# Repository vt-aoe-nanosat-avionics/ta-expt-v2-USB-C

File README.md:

# ta-expt-USB-C
This is a revised version of the Tartan Artibeus Experimental Board with USB C integration.

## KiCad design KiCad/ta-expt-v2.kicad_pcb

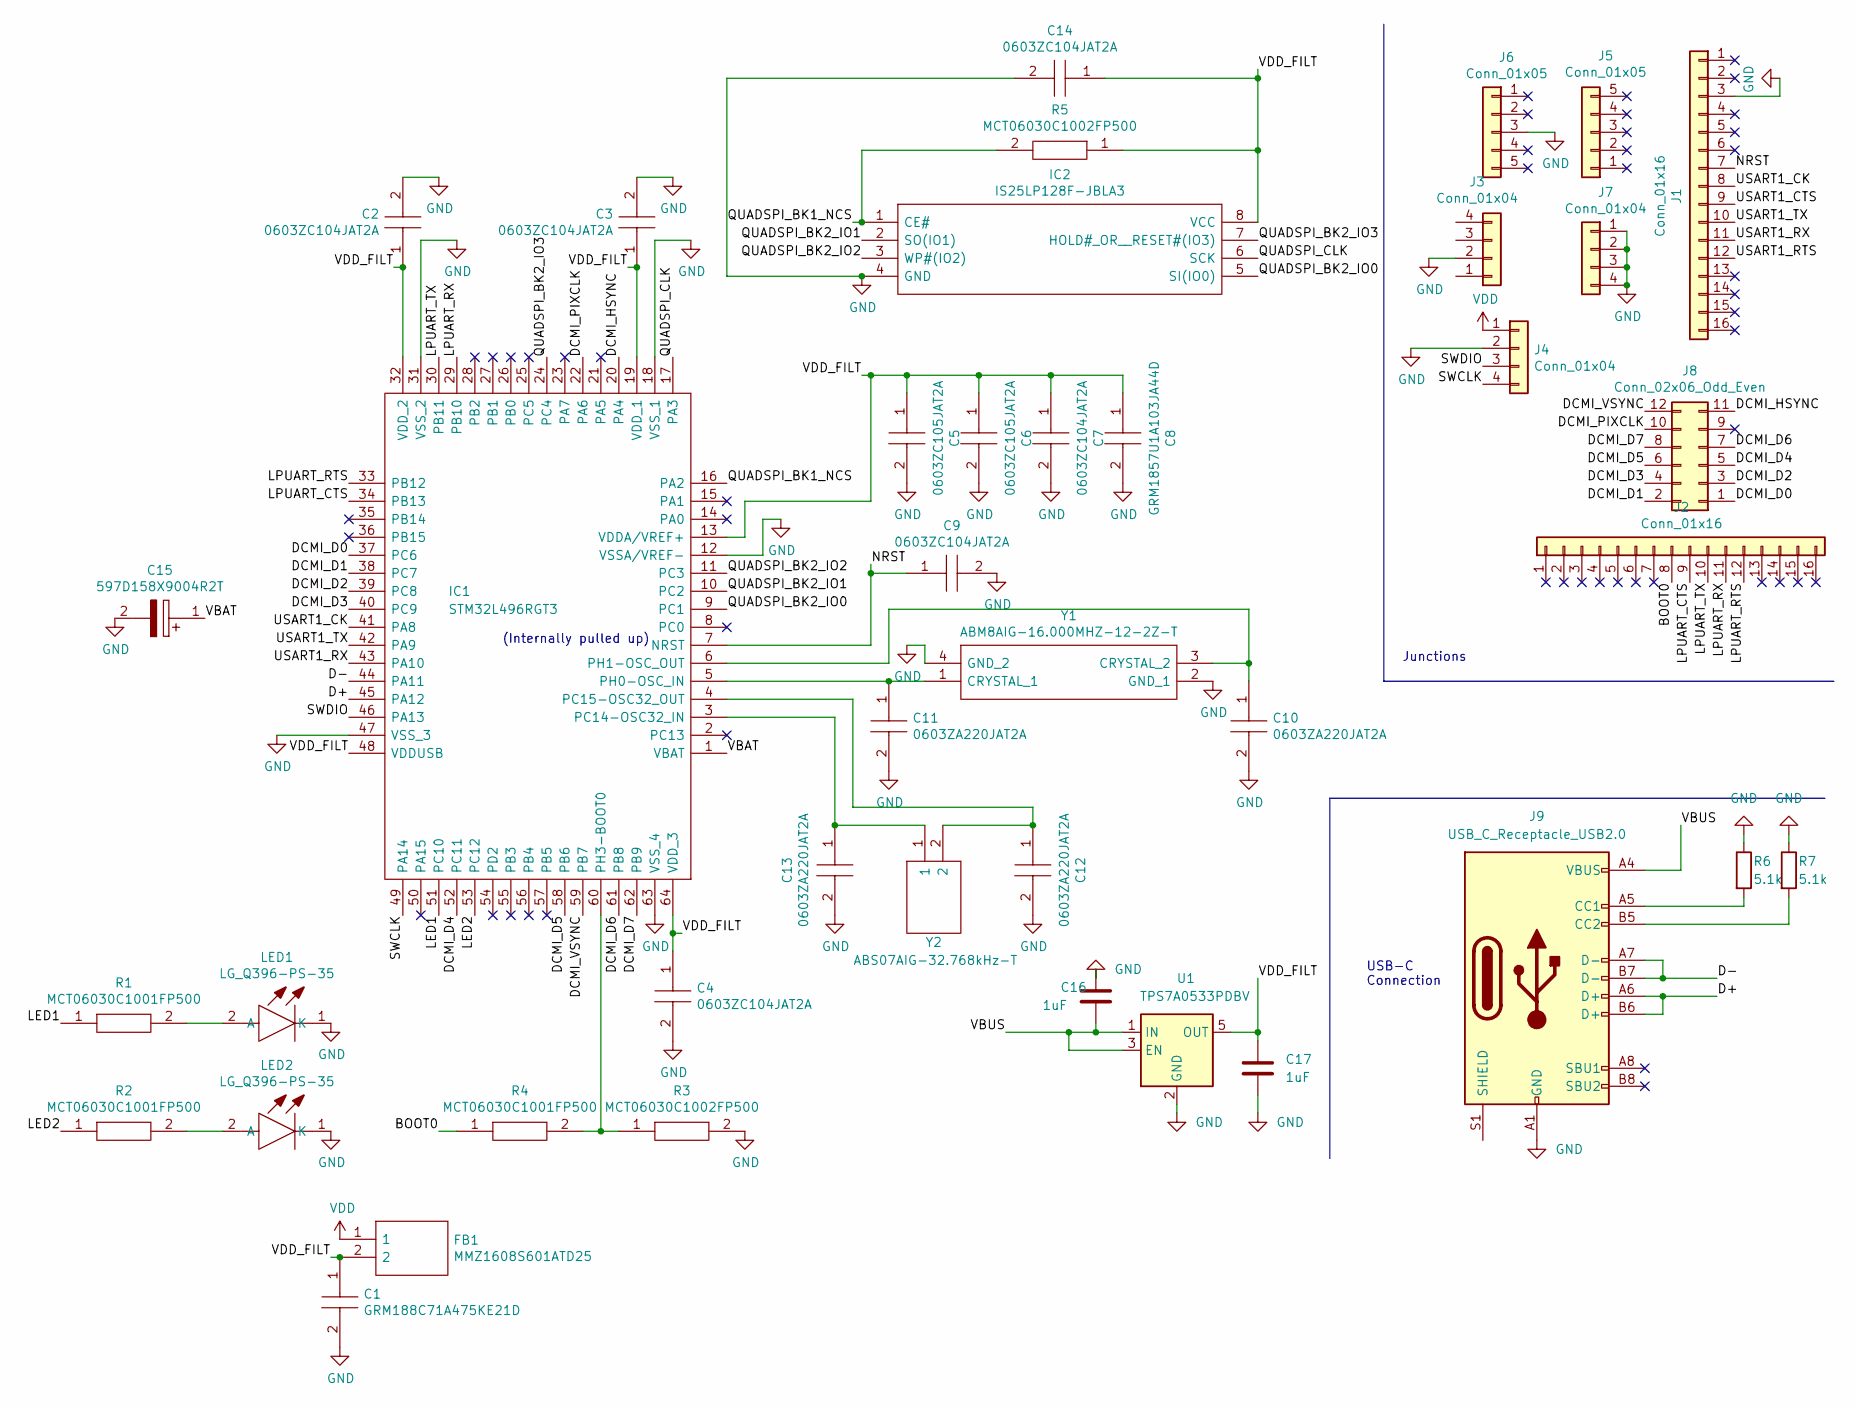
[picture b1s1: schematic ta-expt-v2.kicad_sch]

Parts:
C1: GRM188C71A475KE21D; CAPC1608X90N; Manufacturer_Part_Number GRM188C71A475KE21D; Mouser Part Number 81-GRM188C71A475KE2D
C2, C3, C4, C7, C9, C14: 0603ZC104JAT2A; CAPC1608X90N; Manufacturer_Part_Number 0603ZC104JAT2A; Mouser Part Number 581-0603ZC104JAT2A
C5, C6: 0603ZC105JAT2A; CAPC1608X90N; Manufacturer_Part_Number 0603ZC105JAT2A; Mouser Part Number 581-0603ZC105JAT2A
C8: GRM1857U1A103JA44D; CAPC1608X50N; Manufacturer_Part_Number GRM1857U1A103JA44D; Mouser Part Number 81-GRM1857U1A103JA4D
C10, C11, C12, C13: 0603ZA220JAT2A; CAPC1608X90N; Manufacturer_Part_Number 0603ZA220JAT2A; Mouser Part Number 581-0603ZA220JAT2A
C15: 597D158X9004R2T; CAPPC5660X400N; Manufacturer_Part_Number 597D158X9004R2T; Mouser Part Number 71-597D158X9004R2T
C16, C17: 1uF; CAPC1608X90N
FB1: MMZ1608S601ATD25; BEADC1608X95N; Manufacturer_Part_Number MMZ1608S601ATD25; Mouser Part Number 810-MMZ1608S601ATD25
IC1: STM32L496RGT3; QFP50P1200X1200X160-64N; Manufacturer_Part_Number STM32L496RGT3; Mouser Part Number 511-STM32L496RGT3
IC2: IS25LP128F-JBLA3; SOIC127P790X216-8N; Manufacturer_Part_Number IS25LP128F-JBLA3; Mouser Part Number 870-IS25LP128F-JBLA3
J1, J2: Conn_01x16; PinSocket_1x16_TartanArtibeus
J3, J4: Conn_01x04; PinSocket_4x1_TartanArtibeus
J5, J6: Conn_01x05; PinSocket_1x5_TartanArtibeus
J7: Conn_01x04; MountingHoles_TartanArtibeus
J8: Conn_02x06_Odd_Even; PinSocket_6x2_TartanArtibeus
J9: USB_C_Receptacle_USB2.0; USB_C_CUSB31-CFM2AX-01-X
LED1, LED2: LG_Q396-PS-35; LGQ396PS35; Manufacturer_Part_Number LG Q396-PS-35; Mouser Part Number 720-LGQ396A3964
R1, R2, R4: MCT06030C1001FP500; RESC1608X55N; Manufacturer_Part_Number MCT06030C1001FP500; Mouser Part Number 594-MCT06030C1001FP5
R3, R5: MCT06030C1002FP500; RESC1608X55N; Manufacturer_Part_Number MCT06030C1002FP500; Mouser Part Number 594-MCT06030C1002FP5
R6, R7: 5.1k; RESC1608X55N
U1: TPS7A0533PDBV; SOT-23-5
Y1: ABM8AIG-16.000MHZ-12-2Z-T; ABM8AIG25000MHZ122ZT3; Manufacturer_Part_Number ABM8AIG-16.000MHZ-12-2Z-T; Mouser Part Number 815-ABM8AIG16122ZT
Y2: ABS07AIG-32.768kHz-T; ABS07AIG32768kHz71T; Manufacturer_Part_Number ABS07AIG-32.768kHz-T; Mouser Part Number 815-S07AIG-32.768T

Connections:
/BOOT0: J2.8, R4.1
/D+: IC1.45 (PA12), J9.A6 (D+), J9.B6 (D+)
/D-: IC1.44 (PA11), J9.A7 (D-), J9.B7 (D-)
/DCMI_D0: IC1.37 (PC6), J8.1
/DCMI_D1: IC1.38 (PC7), J8.2
/DCMI_D2: IC1.39 (PC8), J8.3
/DCMI_D3: IC1.40 (PC9), J8.4
/DCMI_D4: IC1.52 (PC11), J8.5
/DCMI_D5: IC1.58 (PB6), J8.6
/DCMI_D6: IC1.61 (PB8), J8.7
/DCMI_D7: IC1.62 (PB9), J8.8
/DCMI_HSYNC: IC1.20 (PA4), J8.11
/DCMI_PIXCLK: IC1.22 (PA6), J8.10
/DCMI_VSYNC: IC1.59 (PB7), J8.12
/LED1: IC1.51 (PC10), R1.1
/LED2: IC1.53 (PC12), R2.1
/LPUART_CTS: IC1.34 (PB13), J2.9
/LPUART_RTS: IC1.33 (PB12), J2.12
/LPUART_RX: IC1.29 (PB10), J2.11
/LPUART_TX: IC1.30 (PB11), J2.10
/NRST: C9.1, IC1.7 (NRST), J1.7
/QUADSPI_BK1_NCS: IC1.16 (PA2), IC2.1 (CE#), R5.2
/QUADSPI_BK2_IO0: IC1.9 (PC1), IC2.5 (SI(IO0))
/QUADSPI_BK2_IO1: IC1.10 (PC2), IC2.2 (SO(IO1))
/QUADSPI_BK2_IO2: IC1.11 (PC3), IC2.3 (WP#(IO2))
/QUADSPI_BK2_IO3: IC1.24 (PC4), IC2.7 (HOLD#_OR__RESET#(IO3))
/QUADSPI_CLK: IC1.17 (PA3), IC2.6 (SCK)
/SWCLK: IC1.49 (PA14), J4.4
/SWDIO: IC1.46 (PA13), J4.3
/USART1_CK: IC1.41 (PA8), J1.8
/USART1_CTS: J1.9
/USART1_RTS: J1.12
/USART1_RX: IC1.43 (PA10), J1.11
/USART1_TX: IC1.42 (PA9), J1.10
/VBAT: C15.1, IC1.1 (VBAT)
/VBUS: C16.2, J9.A4 (VBUS), J9.A9 (VBUS), J9.B4 (VBUS), J9.B9 (VBUS), U1.1 (IN), U1.3 (EN)
/VDD_FILT: C1.1, C2.1, C3.1, C4.1, C5.1, C6.1, C7.1, C8.1, C14.1, C17.1, FB1.2, IC1.13 (VDDA/VREF+), IC1.19 (VDD_1), IC1.32 (VDD_2), IC1.48 (VDDUSB), IC1.64 (VDD_3), IC2.8 (VCC), R5.1, U1.5 (OUT)
GND: C1.2, C2.2, C3.2, C4.2, C5.2, C6.2, C7.2, C8.2, C9.2, C10.2, C11.2, C12.2, C13.2, C14.2, C15.2, C16.1, C17.2, IC1.12 (VSSA/VREF-), IC1.18 (VSS_1), IC1.31 (VSS_2), IC1.47 (VSS_3), IC1.63 (VSS_4), IC2.4 (GND), J1.3, J3.2, J4.2, J6.3, J7.1, J7.2, J7.3, J7.4, J9.A1 (GND), J9.A12 (GND), J9.B1 (GND), J9.B12 (GND), LED1.1 (K), LED2.1 (K), R3.2, R6.1, R7.1, U1.2 (GND), Y1.2 (GND_1), Y1.4 (GND_2)
unnamed: C10.1, IC1.6 (PH1-OSC_OUT), Y1.3 (CRYSTAL_2)
unnamed: C11.1, IC1.5 (PH0-OSC_IN), Y1.1 (CRYSTAL_1)
unnamed: C12.1, IC1.4 (PC15-OSC32_OUT), Y2.2
unnamed: C13.1, IC1.3 (PC14-OSC32_IN), Y2.1
unnamed: IC1.60 (PH3-BOOT0), R3.1, R4.2
unnamed: J9.A5 (CC1), R6.2
unnamed: J9.B5 (CC2), R7.2
unnamed: LED1.2 (A), R1.2
unnamed: LED2.2 (A), R2.2
VDD: FB1.1, J4.1

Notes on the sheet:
Junctions
(Internally pulled up)
USB-C Connection

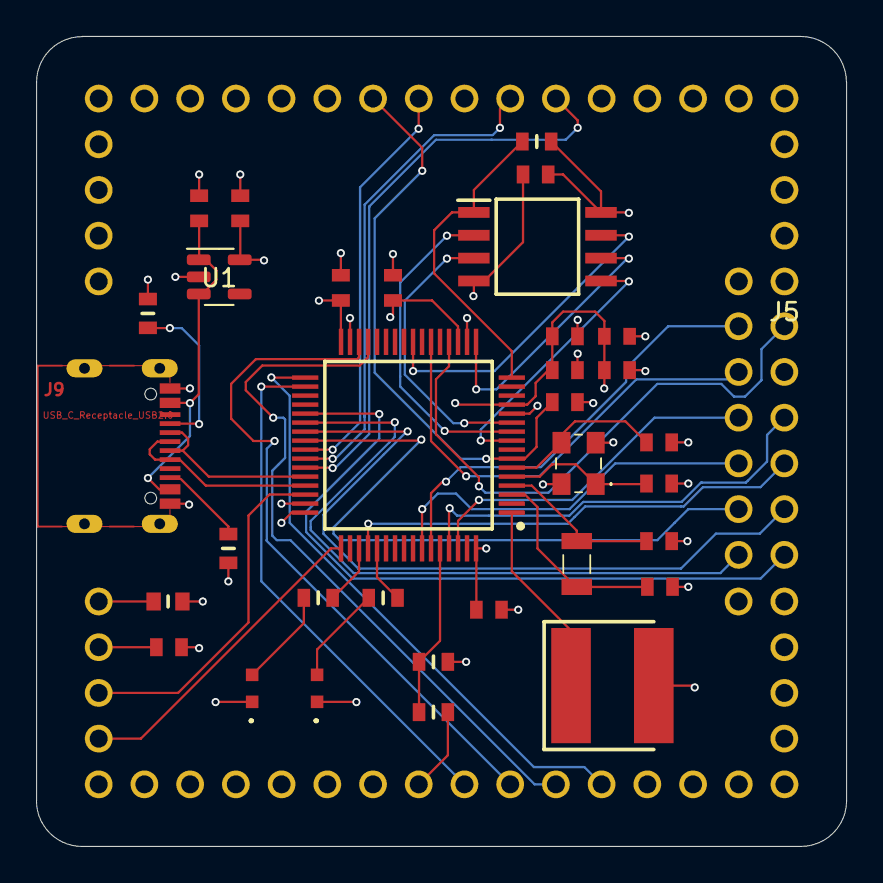
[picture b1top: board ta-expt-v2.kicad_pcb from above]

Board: 4 copper layers, 45.0 x 45.0 mm, 40 parts (1 on the bottom side), 46 nets.

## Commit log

2024-09-10 Add files via upload
    Adding in all the necessary files needed
2024-09-10 Add files via upload
    Gerber Files Added
2024-09-10 Creating Gerber Folder
    Making Gerber Folder
2024-09-10 Rename ta-expt-v2.kicad_prl to KiCad/ta-expt-v2.kicad_prl
2024-09-10 Rename ta-expt-v2.kicad_pro to KiCad/ta-expt-v2.kicad_pro
2024-09-10 Rename fp-info-cache to KiCad/fp-info-cache
2024-09-12 Create Blank_File
